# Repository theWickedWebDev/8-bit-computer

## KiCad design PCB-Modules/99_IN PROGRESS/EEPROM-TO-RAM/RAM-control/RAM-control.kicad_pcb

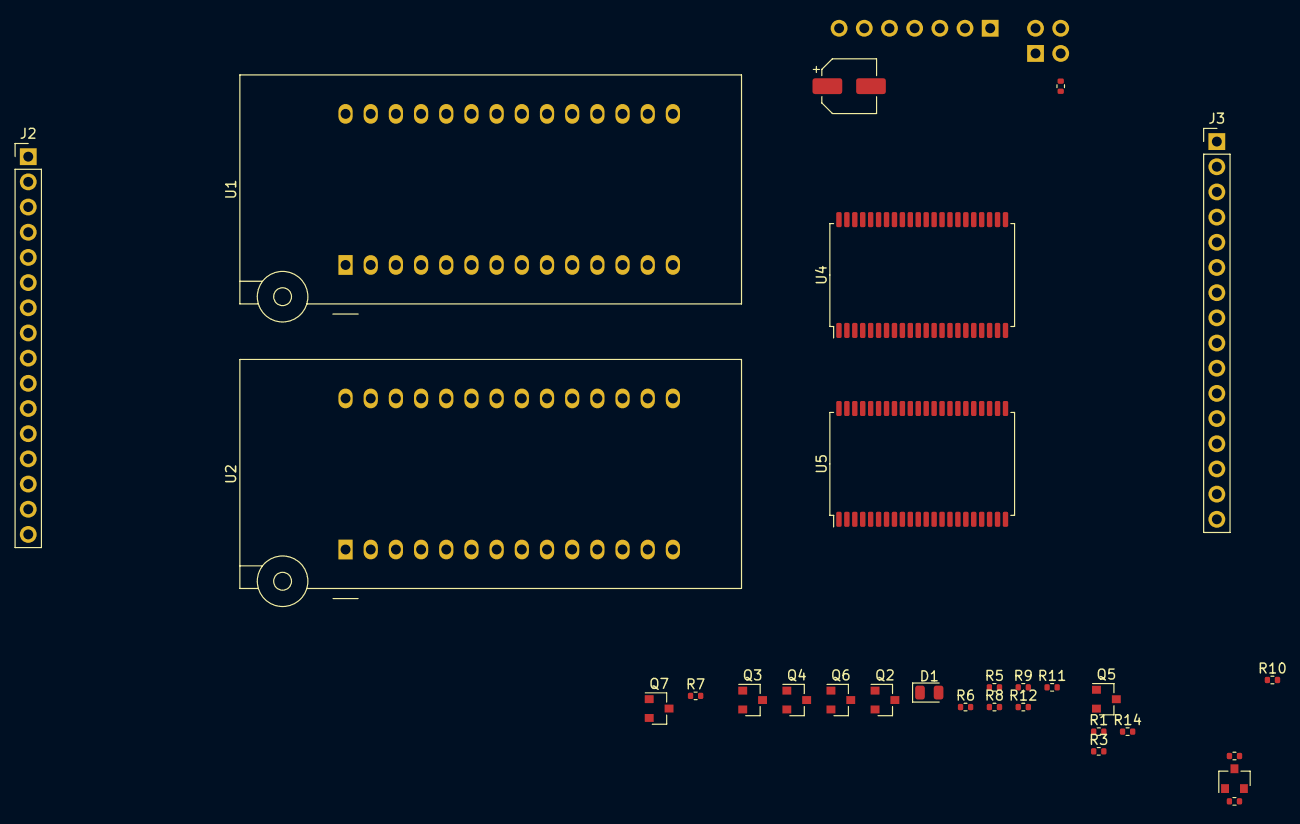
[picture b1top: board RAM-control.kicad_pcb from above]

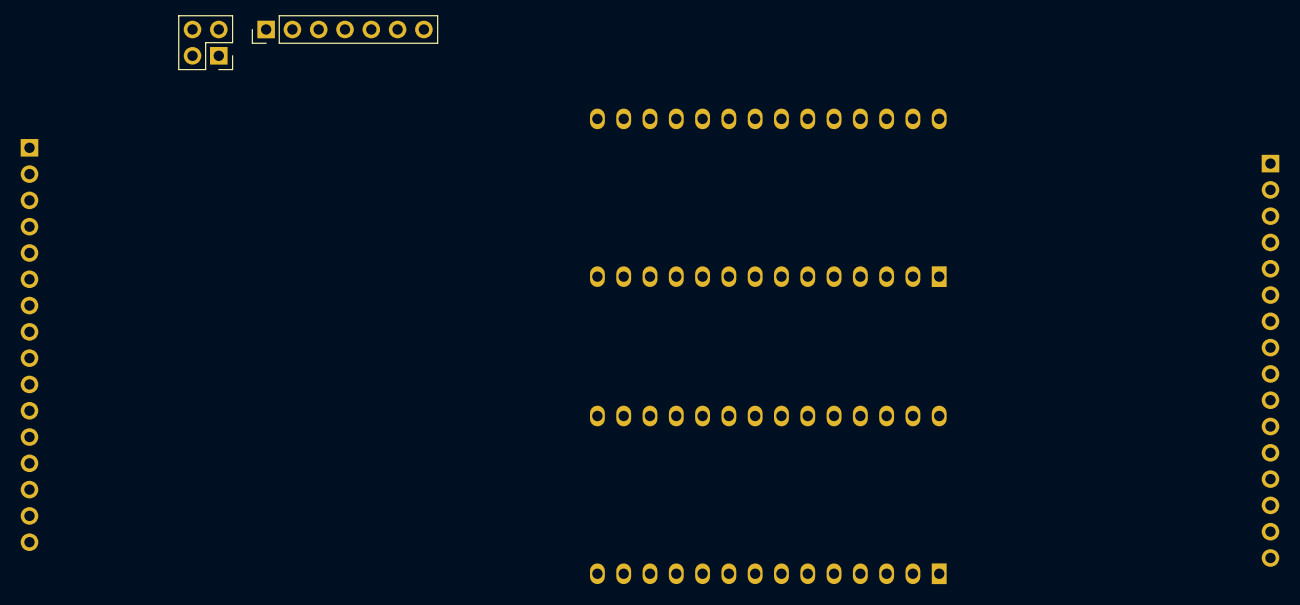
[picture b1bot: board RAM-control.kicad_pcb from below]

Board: 2 copper layers, 31 parts (2 on the bottom side), 55 nets, no tracks yet.

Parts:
C1: SMD-ECAP-5x5.8; CP_Elec_5x5.8
D1: NCD0805R1; LED_0805_2012Metric
J1: Conn_01x07; PinHeader_1x07_P2.54mm_Vertical
J2, J3: Conn_01x16; PinHeader_1x16_P2.54mm_Vertical
J4: Conn_02x02; PinHeader_2x02_P2.54mm_Vertical
Q1: DDTD123YC-7-F; SOT-23
Q2, Q3, Q4, Q5, Q6, Q7: 2N3904S-RTK_PS; SOT-23
R1, R13, R14: 0402WGF1001TCE; R_0402_1005Metric
R2, R10, R11, R12: 0402WGF3901TCE; R_0402_1005Metric
R3, R4, R5, R6, R7, R8, R9: 0603WAF1002T5E; R_0402_1005Metric
U1, U2: 28C256; DIP_Socket-28_W11.9_W12.7_W15.24_W17.78_W18.5_3M_228-1277-0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
U4, U5: IS61WV25616BLL-10TLI; TSOP-II-44_10.16x18.41mm_P0.8mm

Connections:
A00: J2.16, U1.10, U2.10, U4.1, U5.1
A01: J2.15, U1.9, U2.9, U4.2, U5.2
A02: J2.14, U1.8, U2.8, U4.3, U5.3
A03: J2.13, U1.7, U2.7, U4.4, U5.4
A04: J2.12, U1.6, U2.6, U4.5, U5.5
A05: J2.11, U1.5, U2.5, U4.18, U5.18
A06: J2.10, U1.4, U2.4, U4.19, U5.19
A07: J2.9, U1.3, U2.3, U4.20, U5.20
A08: J2.8, U1.25, U2.25, U4.21, U5.21
A09: J2.7, U1.24, U2.24, U4.22, U5.22
A10: J2.6, U1.21, U2.21, U4.23, U5.23
A11: J2.5, U1.23, U2.23, U4.24, U5.24
A12: J2.4, U1.2, U2.2, U4.25, U5.25
A13: J2.3, U1.26, U2.26, U4.26, U5.26
A14: J2.2, U1.1, U2.1, U4.27, U5.27
A16: J4.3, J4.4, R14.2
A17: J4.1, J4.2, R13.2
CLOCK: J1.5, R6.1
D00: J3.16, U1.11, U4.7, U5.7
D01: J3.15, U1.12, U4.8, U5.8
D02: J3.14, U1.13, U4.9, U5.9
D03: J3.13, U1.15, U4.10, U5.10
D04: J3.12, U1.16, U4.13, U5.13
D05: J3.11, U1.17, U4.14, U5.14
D06: J3.10, U1.18, U4.15, U5.15
D07: J3.9, U1.19, U4.16, U5.16
D08: J3.8, U2.11, U4.29, U5.29
D09: J3.7, U2.12, U4.30, U5.30
D10: J3.6, U2.13, U4.31, U5.31
D11: J3.5, U2.15, U4.32, U5.32
D12: J3.4, U2.16, U4.35, U5.35
D13: J3.3, U2.17, U4.36, U5.36
D14: J3.2, U2.18, U4.37, U5.37
D15: J3.1, U2.19, U4.38, U5.38
DATA_REQ: J1.1, R4.1, R7.1
GND: C1.2, J1.6, Q1.2, Q2.1, Q3.1, Q4.1, R1.2, R13.1, R14.1, U1.14, U2.14, U4.12, U4.34, U4.39, U4.40, U4.43, U4.44, U5.12, U5.34, U5.39, U5.40, U5.43, U5.44
unnamed: D1.1, R1.1
unnamed: Q1.1, R4.2
unnamed: Q1.3, R2.2, R8.1
unnamed: Q2.2, R3.2
unnamed: Q2.3, Q5.1
unnamed: Q3.2, R5.2
unnamed: Q3.3, Q6.1
unnamed: Q4.2, R6.2
unnamed: Q4.3, Q7.1
unnamed: Q5.2, R7.2
unnamed: Q6.2, R8.2
unnamed: Q7.2, R9.2
VCC: C1.1, D1.2, J1.7, R2.1, R10.2, R11.2, R12.2, U1.27, U1.28, U2.27, U2.28, U4.11, U4.33, U5.11, U5.33
WE: J1.4, R9.1
~CODE_RAM_EN: Q5.3, R10.1, U4.6
~DATA_RAM_EN: Q6.3, R11.1, U5.6
~OE: J1.3, U1.22, U2.22, U4.41, U5.41
~RAM_WE: Q7.3, R12.1, U4.17, U5.17
~ROM_EN~_A15: J1.2, R3.1, R5.1, U1.20, U2.20, U4.42, U5.42

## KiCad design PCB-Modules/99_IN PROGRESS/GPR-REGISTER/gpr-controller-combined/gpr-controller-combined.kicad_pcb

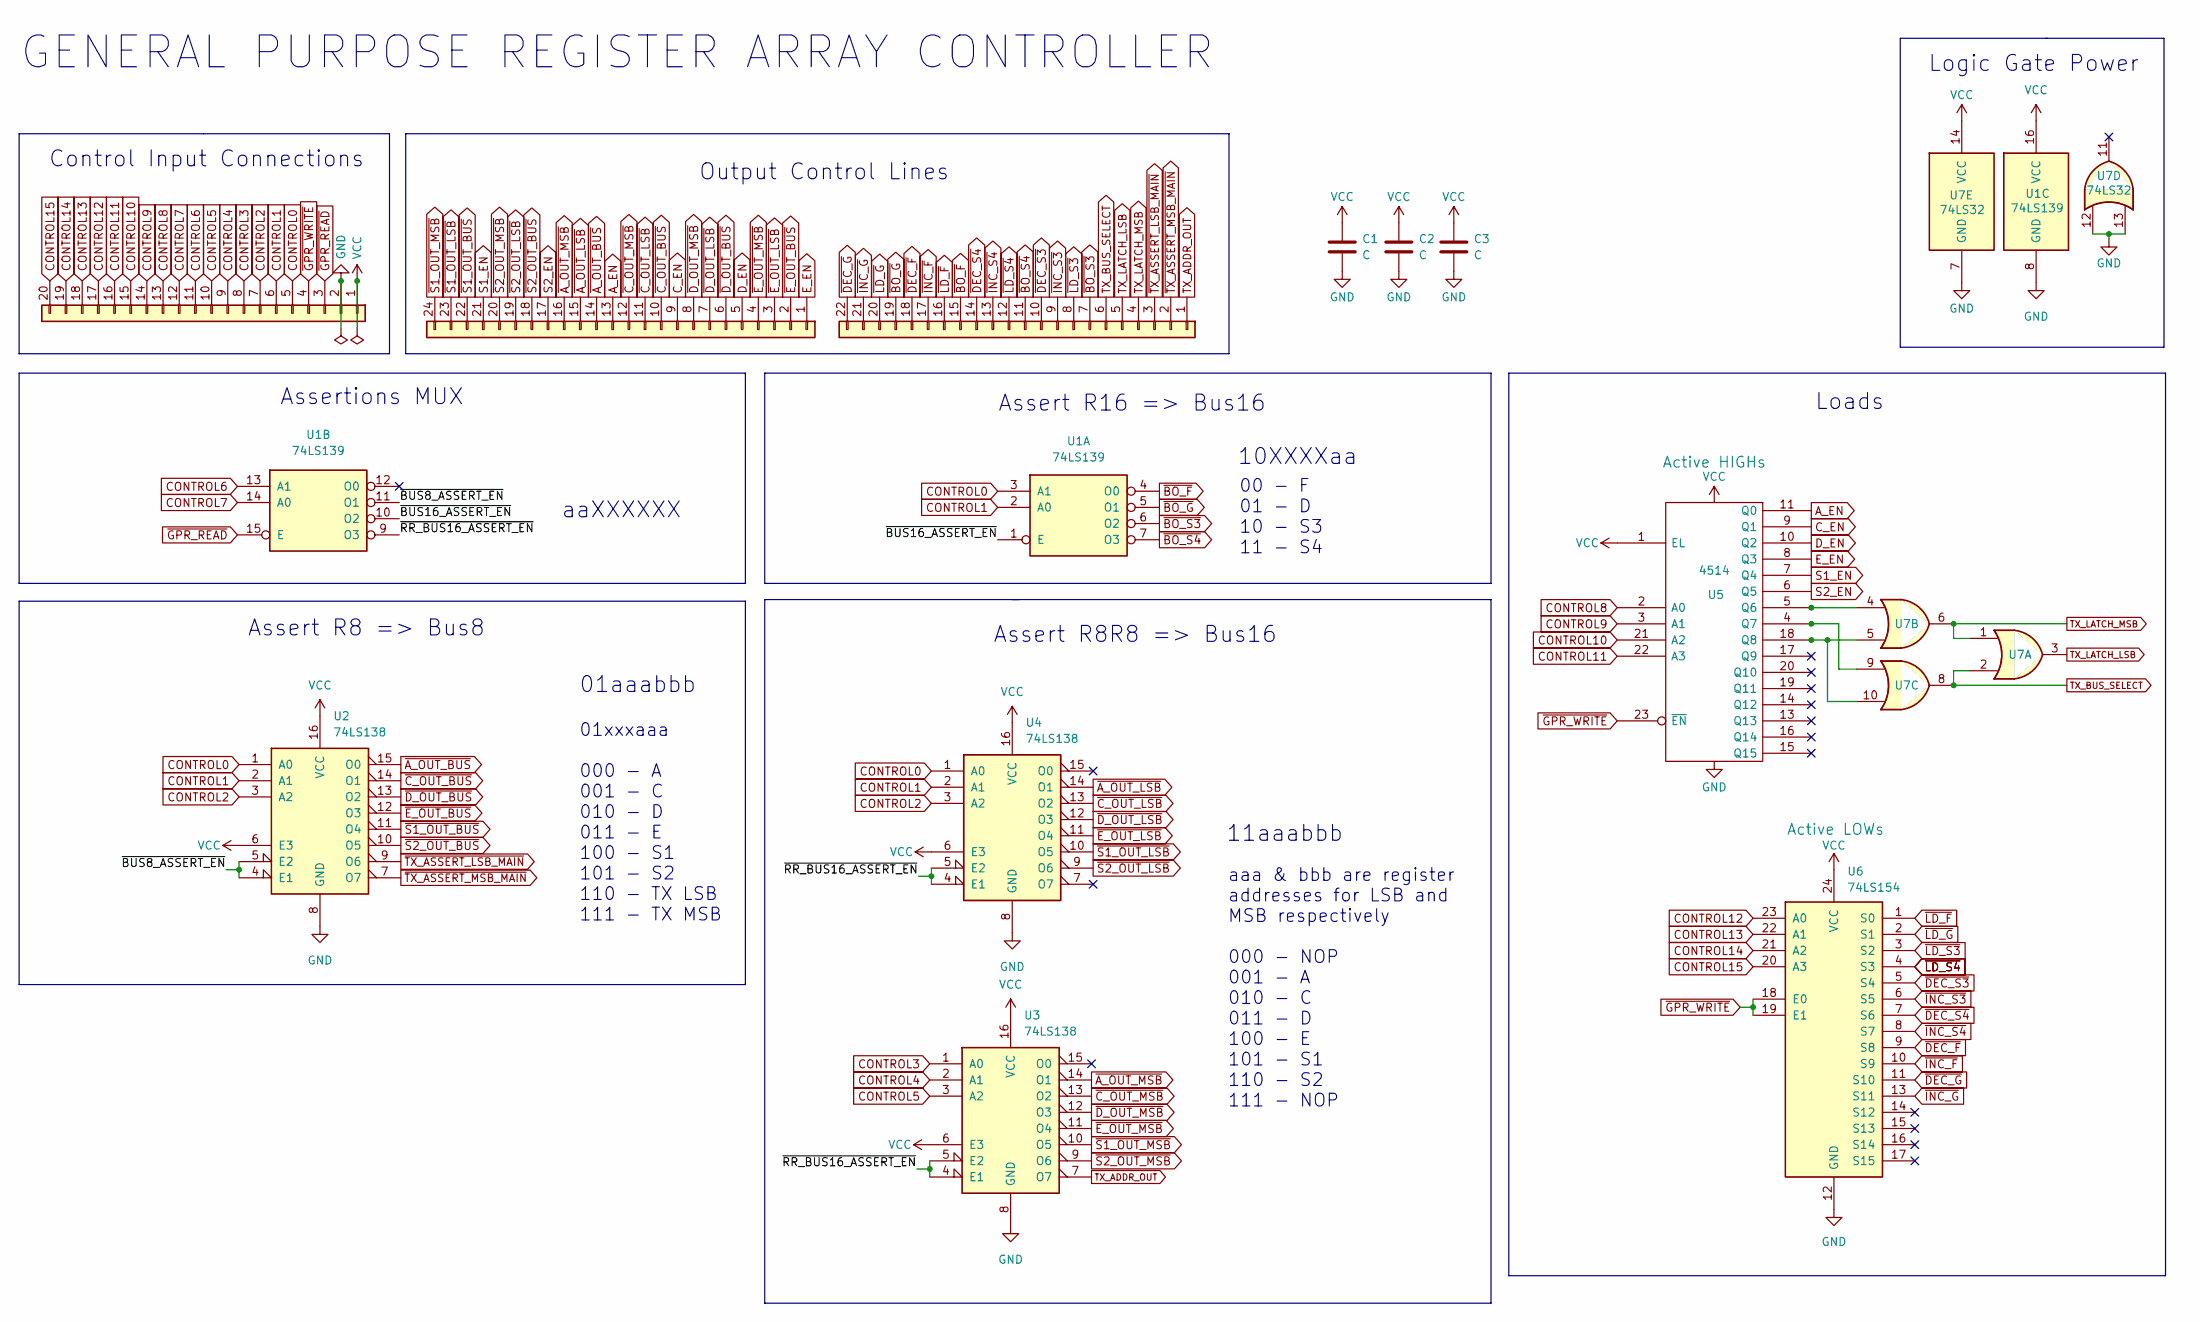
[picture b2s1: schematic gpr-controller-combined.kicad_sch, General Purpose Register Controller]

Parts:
C1, C2, C3: C; C_0805_2012Metric
J1: Conn_01x21; PinHeader_1x20_P2.54mm_Vertical
J2: Conn_01x24; PinHeader_1x24_P2.54mm_Vertical
J3: Conn_01x22; PinHeader_1x22_P2.54mm_Vertical
U1: 74LS139; TSSOP-16_4.4x5mm_P0.65mm
U2, U3, U4: 74LS138; TSSOP-16_4.4x5mm_P0.65mm
U5: 4514; SOP-24_7.5x15.4mm_P1.27mm
U6: 74LS154; SOP-24_7.5x15.4mm_P1.27mm
U7: 74LS32; TSSOP-14_4.4x5mm_P0.65mm

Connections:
/~BUS8_ASSERT_EN: U1.11 (O1), U2.4 (E1), U2.5 (E2)
/~BUS16_ASSERT_EN: U1.1 (E), U1.10 (O2)
/~RR_BUS16_ASSERT_EN: U1.9 (O3), U3.4 (E1), U3.5 (E2), U4.4 (E1), U4.5 (E2)
A_EN: J2.13, U5.11 (Q0)
CONTROL0: J1.5, U1.3 (A1), U2.1 (A0), U4.1 (A0)
CONTROL1: J1.6, U1.2 (A0), U2.2 (A1), U4.2 (A1)
CONTROL2: J1.7, U2.3 (A2), U4.3 (A2)
CONTROL3: J1.8, U3.1 (A0)
CONTROL4: J1.9, U3.2 (A1)
CONTROL5: J1.10, U3.3 (A2)
CONTROL6: J1.11, U1.13 (A1)
CONTROL7: J1.12, U1.14 (A0)
CONTROL8: J1.13, U5.2 (A0)
CONTROL9: J1.14, U5.3 (A1)
CONTROL10: J1.15, U5.21 (A2)
CONTROL11: J1.16, U5.22 (A3)
CONTROL12: J1.17, U6.23 (A0)
CONTROL13: J1.18, U6.22 (A1)
CONTROL14: J1.19, U6.21 (A2)
CONTROL15: J1.20, U6.20 (A3)
C_EN: J2.9, U5.9 (Q1)
D_EN: J2.5, U5.10 (Q2)
E_EN: J2.1, U5.8 (Q3)
GND: C1.2, C2.2, C3.2, J1.2, U1.8 (GND), U2.8 (GND), U3.8 (GND), U4.8 (GND), U5.12 (Vss), U6.12 (GND), U7.7 (GND), U7.12, U7.13
unnamed: U5.4 (Q7), U7.9
unnamed: U5.5 (Q6), U7.4
unnamed: U5.18 (Q8), U7.5, U7.10
S1_EN: J2.21, U5.7 (Q4)
S2_EN: J2.17, U5.6 (Q5)
TX_ADDR_OUT: J3.1, U3.7 (O7)
TX_BUS_SELECT: J3.6, U7.2, U7.8
TX_LATCH_LSB: J3.5, U7.3
TX_LATCH_MSB: J3.4, U7.1, U7.6
VCC: C1.1, C2.1, C3.1, J1.1, U1.16 (VCC), U2.6 (E3), U2.16 (VCC), U3.6 (E3), U3.16 (VCC), U4.6 (E3), U4.16 (VCC), U5.1 (EL), U5.24 (Vdd), U6.24 (VCC), U7.14 (VCC)
~A_OUT_BUS: J2.14, U2.15 (O0)
~A_OUT_LSB: J2.15, U4.14 (O1)
~A_OUT_MSB: J2.16, U3.14 (O1)
~BO_F: J3.15, U1.4 (O0)
~BO_G: J3.19, U1.5 (O1)
~BO_S3: J3.7, U1.6 (O2)
~BO_S4: J3.11, U1.7 (O3)
~C_OUT_BUS: J2.10, U2.14 (O1)
~C_OUT_LSB: J2.11, U4.13 (O2)
~C_OUT_MSB: J2.12, U3.13 (O2)
~DEC_F: J3.18, U6.9 (S8)
~DEC_G: J3.22, U6.11 (S10)
~DEC_S3: J3.10, U6.5 (S4)
~DEC_S4: J3.14, U6.7 (S6)
~D_OUT_BUS: J2.6, U2.13 (O2)
~D_OUT_LSB: J2.7, U4.12 (O3)
~D_OUT_MSB: J2.8, U3.12 (O3)
~E_OUT_BUS: J2.2, U2.12 (O3)
~E_OUT_LSB: J2.3, U4.11 (O4)
~E_OUT_MSB: J2.4, U3.11 (O4)
~GPR_READ: J1.3, U1.15 (E)
~GPR_WRITE: J1.4, U5.23 (~EN), U6.18 (E0), U6.19 (E1)
~INC_F: J3.17, U6.10 (S9)
~INC_G: J3.21, U6.13 (S11)
~INC_S3: J3.9, U6.6 (S5)
~INC_S4: J3.13, U6.8 (S7)
~LD_F: J3.16, U6.1 (S0)
~LD_G: J3.20, U6.2 (S1)
~LD_S3: J3.8, U6.3 (S2)
~LD_S4: J3.12, U6.4 (S3)
~S1_OUT_BUS: J2.22, U2.11 (O4)
~S1_OUT_LSB: J2.23, U4.10 (O5)
~S1_OUT_MSB: J2.24, U3.10 (O5)
~S2_OUT_BUS: J2.18, U2.10 (O5)
~S2_OUT_LSB: J2.19, U4.9 (O6)
~S2_OUT_MSB: J2.20, U3.9 (O6)
~TX_ASSERT_LSB_MAIN: J3.3, U2.9 (O6)
~TX_ASSERT_MSB_MAIN: J3.2, U2.7 (O7)

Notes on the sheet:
01aaabbb
Assert R8 => Bus8
Loads
00 - F 01 - D 10 - S3 11 - S4
11aaabbb
10XXXXaa
aaa & bbb are register addresses for LSB and MSB respectively 000 - NOP 001 - A 010 - C 011 - D 100 - E 101 - S1 110 - S2 111 - NOP
Assert R16 => Bus16
aaXXXXXX
GENERAL PURPOSE REGISTER ARRAY CONTROLLER
Control Input Connections
Assertions MUX
Output Control Lines
01xxxaaa 000 - A 001 - C 010 - D 011 - E 100 - S1 101 - S2 110 - TX LSB 111 - TX MSB
Assert R8R8 => Bus16
Logic Gate Power

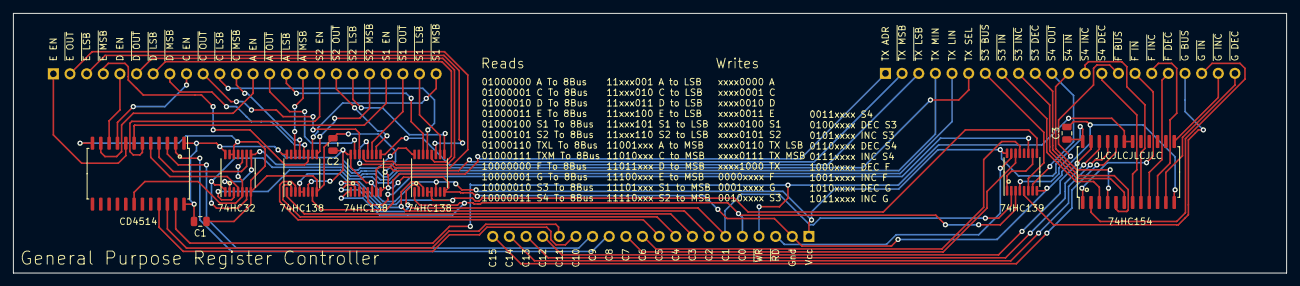
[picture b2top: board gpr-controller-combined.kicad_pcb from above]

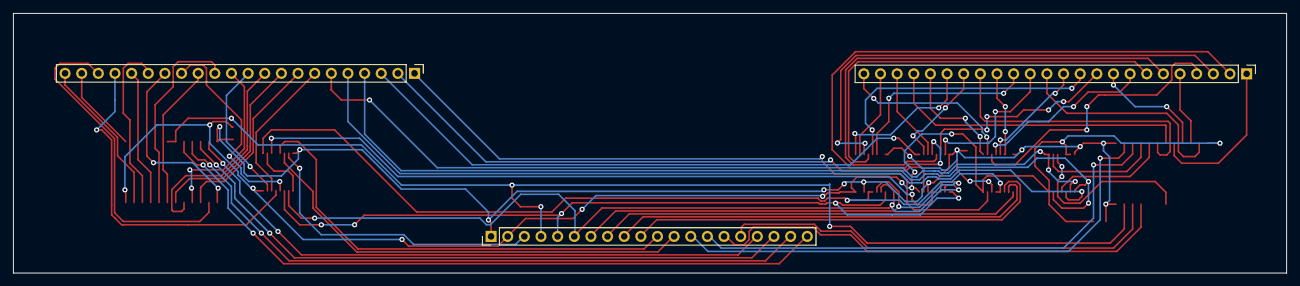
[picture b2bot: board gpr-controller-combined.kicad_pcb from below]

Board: 2 copper layers, 194.3 x 39.6 mm, 13 parts (3 on the bottom side), 72 nets.

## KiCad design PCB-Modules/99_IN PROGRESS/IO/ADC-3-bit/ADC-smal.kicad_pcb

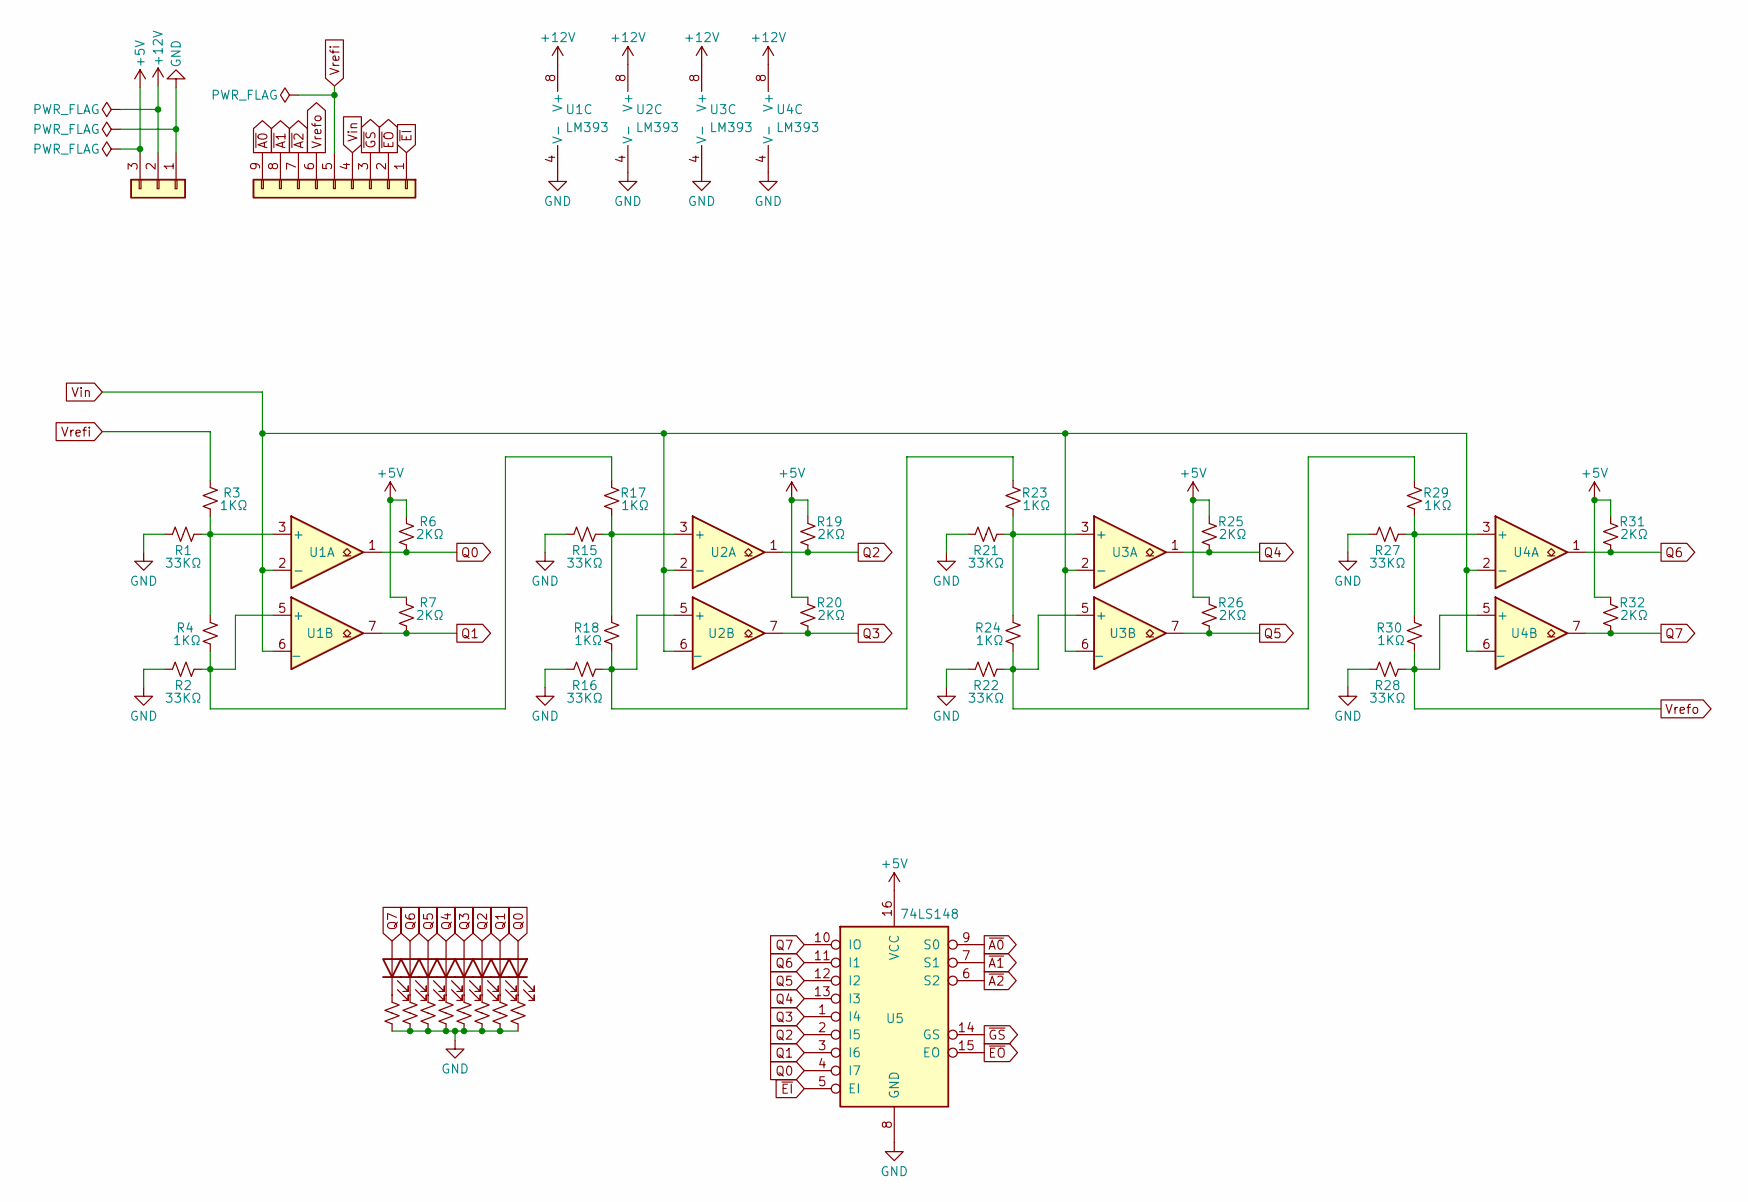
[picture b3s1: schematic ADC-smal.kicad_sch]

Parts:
D1, D2, D3, D4, D5, D6, D7, D8: LED; LED_0805_2012Metric
J1: Conn_01x03; PinHeader_1x03_P2.54mm_Vertical
J2: Conn_01x09; PinHeader_1x09_P2.54mm_Vertical
R1, R2, R3, R4, R5, R6, R7, R8, R9, R10, R11, R12, R13, R14, R15, R16, R17, R18, R19, R20, R21, R22, R23, R24, R25, R26, R27, R28, R29, R30, R31, R32: R_Small_US; R_0805_2012Metric
U1, U2, U3, U4: LM393; SOIC-8_3.9x4.9mm_P1.27mm
U5: 74LS148; SOIC-16_3.9x9.9mm_P1.27mm

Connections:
+5V: J1.3, R6.2, R7.2, R19.2, R20.2, R25.2, R26.2, R31.2, R32.2, U5.16 (VCC)
+12V: J1.2, U1.8 (V+), U2.8 (V+), U3.8 (V+), U4.8 (V+)
GND: J1.1, R1.1, R2.1, R5.2, R8.2, R9.2, R10.2, R11.2, R12.2, R13.2, R14.2, R15.1, R16.1, R21.1, R22.1, R27.1, R28.1, U1.4 (V-), U2.4 (V-), U3.4 (V-), U4.4 (V-), U5.8 (GND)
unnamed: D1.1 (K), R5.1
unnamed: D2.1 (K), R8.1
unnamed: D3.1 (K), R9.1
unnamed: D4.1 (K), R10.1
unnamed: D5.1 (K), R11.1
unnamed: D6.1 (K), R12.1
unnamed: D7.1 (K), R13.1
unnamed: D8.1 (K), R14.1
unnamed: R1.2, R3.2, R4.1, U1.3 (+)
unnamed: R15.2, R17.2, R18.1, U2.3 (+)
unnamed: R16.2, R18.2, R23.1, U2.5 (+)
unnamed: R2.2, R4.2, R17.1, U1.5 (+)
unnamed: R21.2, R23.2, R24.1, U3.3 (+)
unnamed: R22.2, R24.2, R29.1, U3.5 (+)
unnamed: R27.2, R29.2, R30.1, U4.3 (+)
Q0: D8.2 (A), R6.1, U1.1, U5.4 (I7)
Q1: D7.2 (A), R7.1, U1.7, U5.3 (I6)
Q2: D6.2 (A), R19.1, U2.1, U5.2 (I5)
Q3: D5.2 (A), R20.1, U2.7, U5.1 (I4)
Q4: D4.2 (A), R25.1, U3.1, U5.13 (I3)
Q5: D3.2 (A), R26.1, U3.7, U5.12 (I2)
Q6: D2.2 (A), R31.1, U4.1, U5.11 (I1)
Q7: D1.2 (A), R32.1, U4.7, U5.10 (IO)
Vin: J2.4, U1.2 (-), U1.6 (_), U2.2 (-), U2.6 (_), U3.2 (-), U3.6 (_), U4.2 (-), U4.6 (_)
Vrefi: J2.5, R3.1
Vrefo: J2.6, R28.2, R30.2, U4.5 (+)
~A0: J2.9, U5.9 (S0)
~A1: J2.8, U5.7 (S1)
~A2: J2.7, U5.6 (S2)
~EI: J2.1, U5.5 (EI)
~EO: J2.2, U5.15 (EO)
~GS: J2.3, U5.14 (GS)

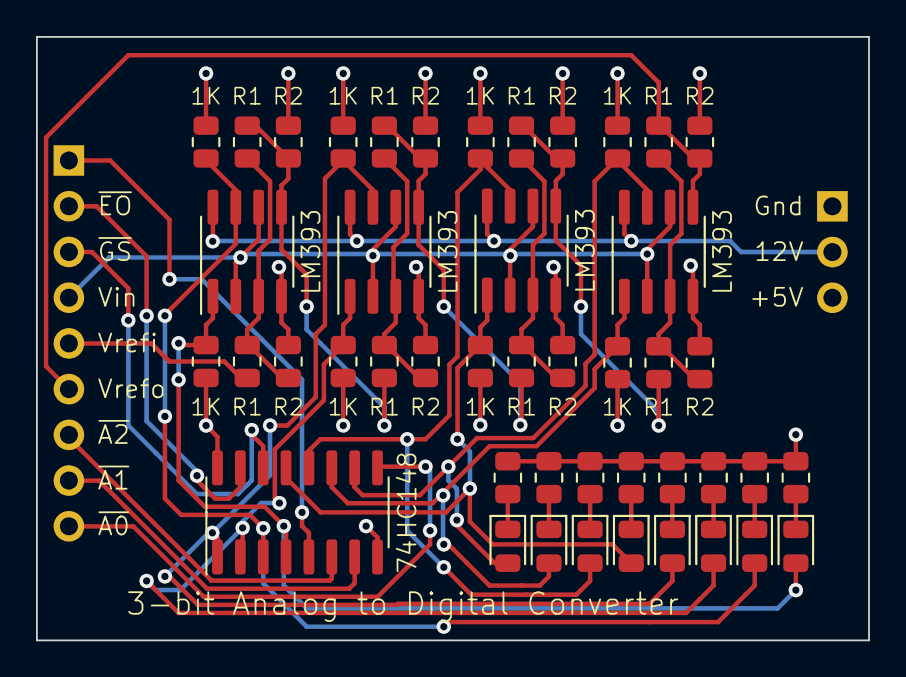
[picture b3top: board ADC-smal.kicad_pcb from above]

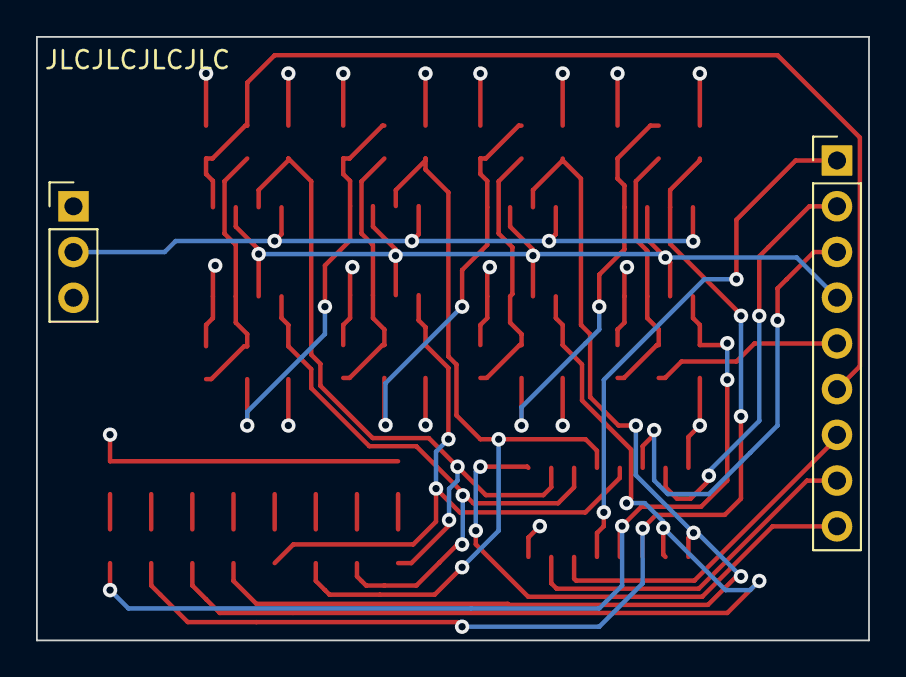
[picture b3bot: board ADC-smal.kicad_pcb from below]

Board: 4 copper layers, 46.2 x 33.5 mm, 47 parts (2 on the bottom side), 35 nets.

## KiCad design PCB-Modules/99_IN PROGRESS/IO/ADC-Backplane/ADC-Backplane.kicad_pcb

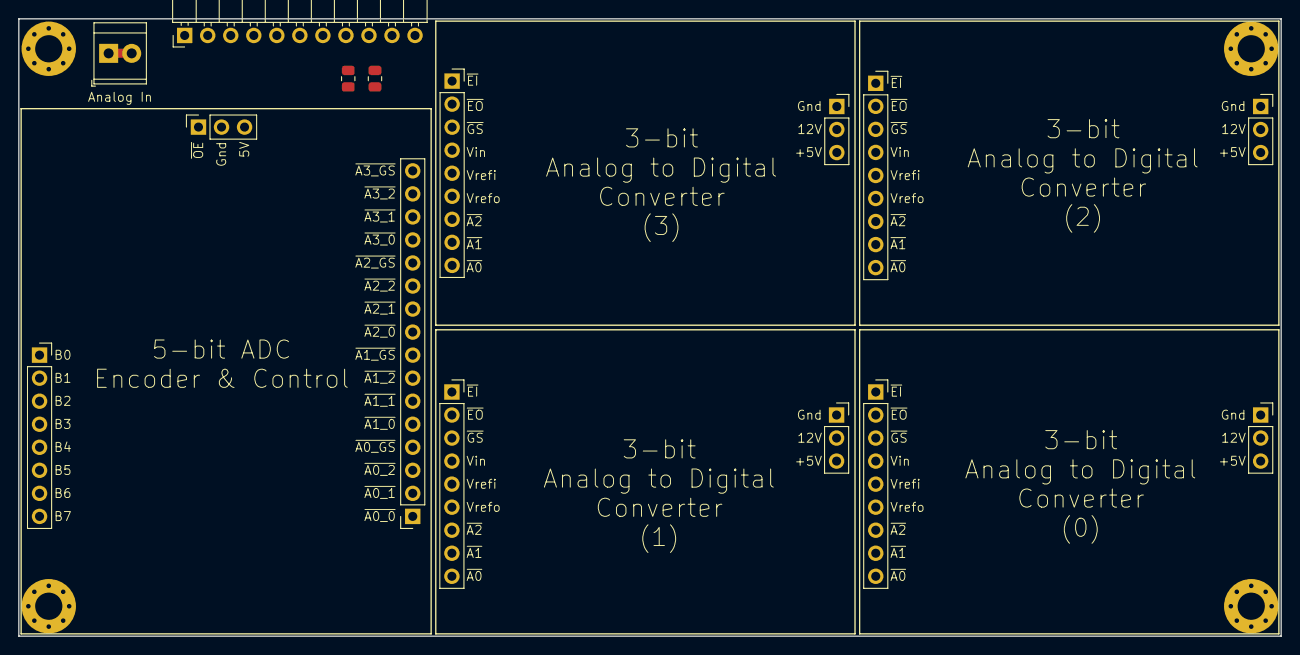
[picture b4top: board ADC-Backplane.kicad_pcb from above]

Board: 4 copper layers, 139.2 x 68.1 mm, 15 parts (0 on the bottom side), 33 nets.

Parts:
J1: Conn_01x11; PinHeader_1x11_P2.54mm_Horizontal
J2, J4, J6, J8: Conn_01x09; PinSocket_1x09_P2.54mm_Vertical
J3, J5, J7, J9, J10: Conn_01x03; PinSocket_1x03_P2.54mm_Vertical
J11: Conn_01x16; PinSocket_1x16_P2.54mm_Vertical
J12: Conn_01x08; PinSocket_1x08_P2.54mm_Vertical
J13: Screw_Terminal_01x02; TerminalBlock_TE_282834-2_1x02_P2.54mm_Horizontal
R1, R2: R_Small_US; R_0805_2012Metric

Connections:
BUS0: J1.4, J12.1
BUS1: J1.5, J12.2
BUS2: J1.6, J12.3
BUS3: J1.7, J12.4
BUS4: J1.8, J12.5
BUS5: J1.9, J12.6
BUS6: J1.10, J12.7
BUS7: J1.11, J12.8
GND: J1.2, J3.1, J5.1, J7.1, J8.1, J9.1, R2.2
unnamed: J2.5, J4.6
unnamed: J2.1, J4.2
unnamed: J4.5, J6.6
unnamed: J6.1, J8.2
unnamed: J4.1, J6.2
unnamed: J6.5, J8.6
unnamed: J8.5, R1.1, R2.1
~A0_0: J8.9, J11.1
~A0_1: J8.8, J11.2
~A0_2: J8.7, J11.3
~A0_GS: J8.3, J11.4
~A1_0: J6.9, J11.5
~A1_1: J6.8, J11.6
~A1_2: J6.7, J11.7
~A1_GS: J6.3, J11.8
~A2_0: J4.9, J11.9
~A2_1: J4.8, J11.10
~A2_2: J4.7, J11.11
~A2_GS: J4.3, J11.12
~A3_0: J2.9, J11.13
~A3_1: J2.8, J11.14
~A3_2: J2.7, J11.15
~A3_GS: J2.3, J11.16
~ANALOG_IN: J2.4, J4.4, J6.4, J8.4, J13.1, J13.2

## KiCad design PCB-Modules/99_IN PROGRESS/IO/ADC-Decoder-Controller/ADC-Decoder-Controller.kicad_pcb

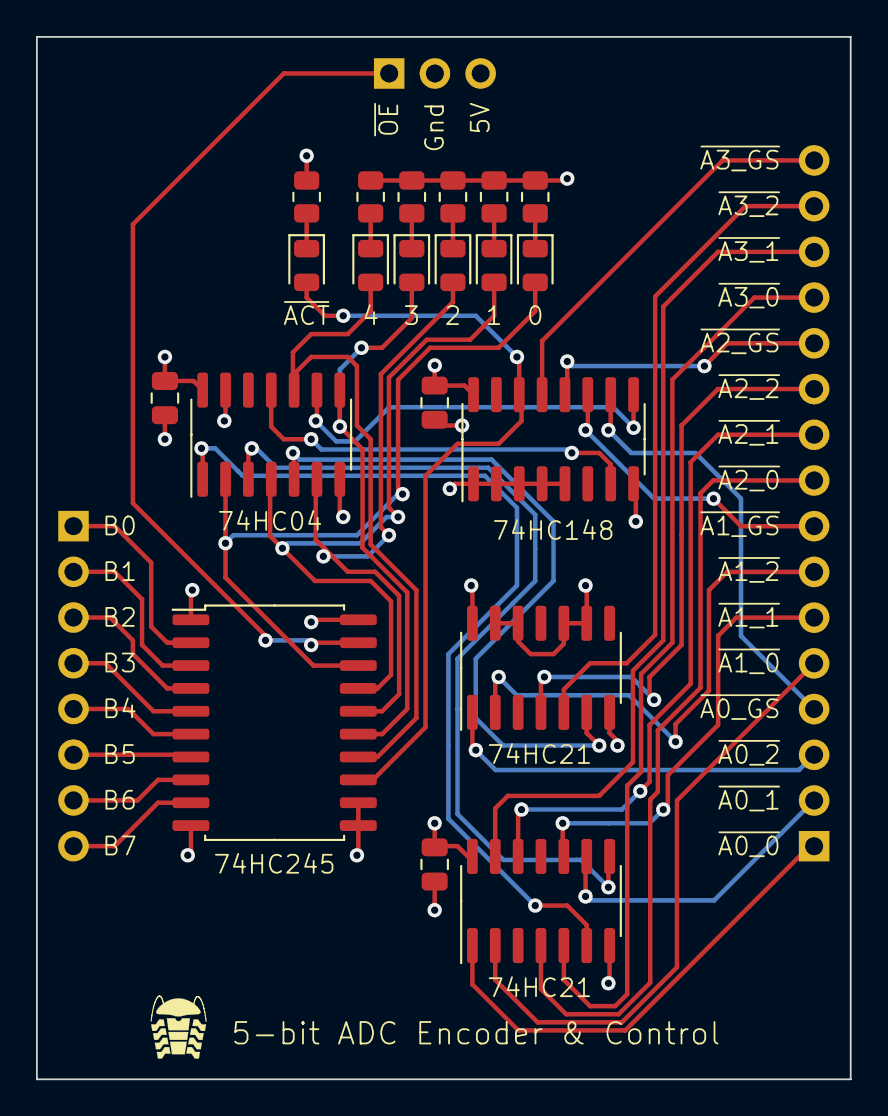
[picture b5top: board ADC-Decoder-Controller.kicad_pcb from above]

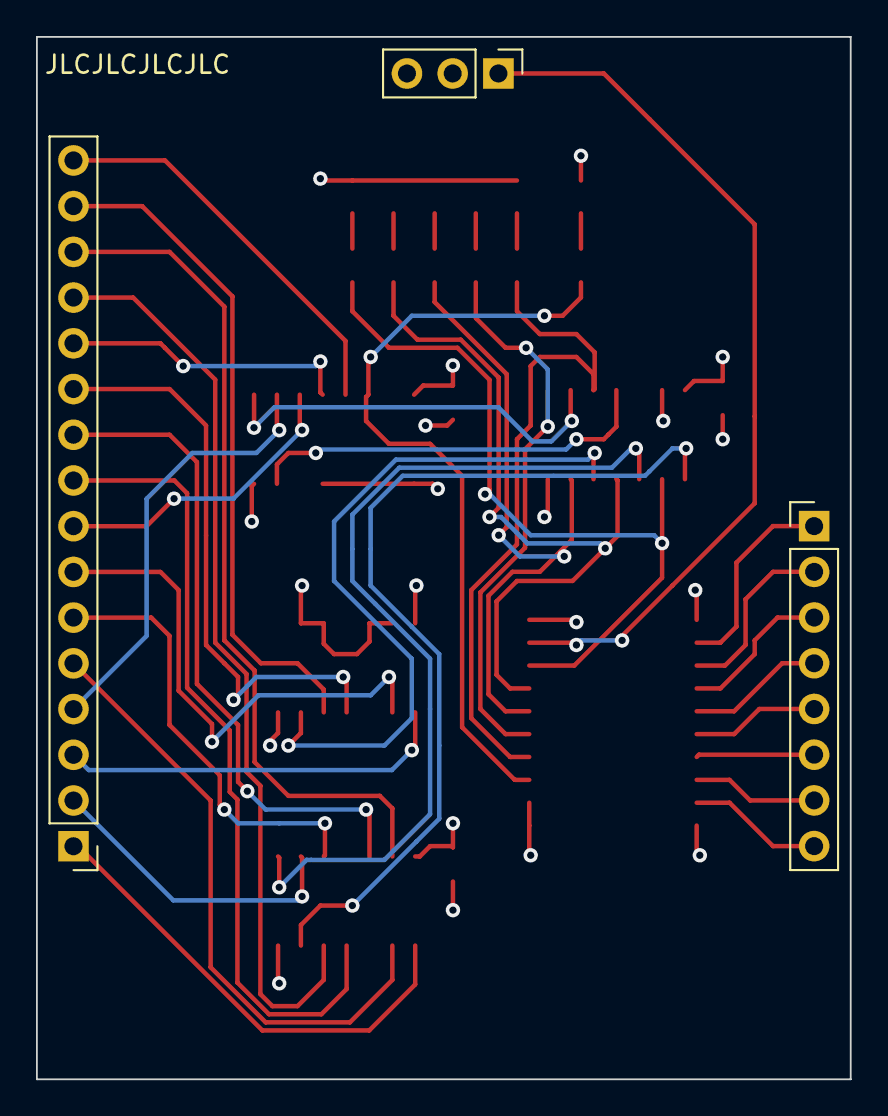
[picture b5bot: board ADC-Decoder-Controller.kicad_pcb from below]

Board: 4 copper layers, 45.2 x 57.9 mm, 23 parts (3 on the bottom side), 44 nets.

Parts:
C1, C2, C3: C_Small; C_0805_2012Metric
D1, D2, D3, D4, D5, D6: LED; LED_0805_2012Metric
J1: Conn_01x08; PinHeader_1x08_P2.54mm_Vertical
J2: Conn_01x16; PinHeader_1x16_P2.54mm_Vertical
J3: Conn_01x03; PinHeader_1x03_P2.54mm_Vertical
R3, R4, R5, R6, R7, R8: R_Small_US; R_0805_2012Metric
U1, U2: 74LS21; SOIC-14_3.9x8.7mm_P1.27mm
U3: 74LS148; SOIC-16_3.9x9.9mm_P1.27mm
U4: 74LS04; SOIC-14_3.9x8.7mm_P1.27mm
U5: 74LS245; SOIC-20W_7.5x12.8mm_P1.27mm

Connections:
+5V: C1.1, C2.1, C3.1, J3.3, U1.14 (VCC), U2.14 (VCC), U3.1 (I4), U3.2 (I5), U3.3 (I6), U3.4 (I7), U3.5 (EI), U3.16 (VCC), U4.14 (VCC), U5.20 (VCC)
BUS0: J1.1, U5.2 (A0)
BUS1: J1.2, U5.3 (A1)
BUS2: J1.3, U5.4 (A2)
BUS3: J1.4, U5.5 (A3)
BUS4: J1.5, U5.6 (A4)
BUS5: J1.6, U5.7 (A5)
BUS6: J1.7, U5.8 (A6)
BUS7: J1.8, U5.9 (A7)
D0: D6.2 (A), U4.2, U5.18 (B0)
D1: D5.2 (A), U4.4, U5.17 (B1)
D2: D4.2 (A), U4.6, U5.16 (B2)
D3: D3.2 (A), U4.8, U5.15 (B3)
D4: D2.2 (A), U4.10, U5.14 (B4)
GND: C1.2, C2.2, C3.2, J3.2, R3.2, R4.2, R5.2, R6.2, R7.2, R8.2, U1.7 (GND), U2.7 (GND), U2.9, U2.10, U2.12, U2.13, U3.8 (GND), U4.7 (GND), U4.13, U5.1 (A->B), U5.10 (GND), U5.11 (B7), U5.12 (B6)
unnamed: D1.1 (K), R3.1
unnamed: D2.1 (K), R4.1
unnamed: D3.1 (K), R5.1
unnamed: D4.1 (K), R6.1
unnamed: D5.1 (K), R7.1
unnamed: D6.1 (K), R8.1
unnamed: U1.6, U4.1
unnamed: U1.8, U4.3
unnamed: U2.6, U4.5
unnamed: U3.7 (S1), U4.11
unnamed: U3.9 (S0), U4.9
~A0_0: J2.1, U1.1
~A0_1: J2.2, U1.9
~A0_2: J2.3, U2.1
~A0_GS: J2.4, U3.10 (IO)
~A1_0: J2.5, U1.2
~A1_1: J2.6, U1.10
~A1_2: J2.7, U2.2
~A1_GS: J2.8, U3.11 (I1)
~A2_0: J2.9, U1.4
~A2_1: J2.10, U1.12
~A2_2: J2.11, U2.4
~A2_GS: J2.12, U3.12 (I2)
~A3_0: J2.13, U1.5
~A3_1: J2.14, U1.13
~A3_2: J2.15, U2.5
~A3_GS: J2.16, U3.13 (I3)
~ACTIVE: D1.2 (A), U3.14 (GS), U5.13 (B5)
~OE: J3.1, U5.19 (CE)

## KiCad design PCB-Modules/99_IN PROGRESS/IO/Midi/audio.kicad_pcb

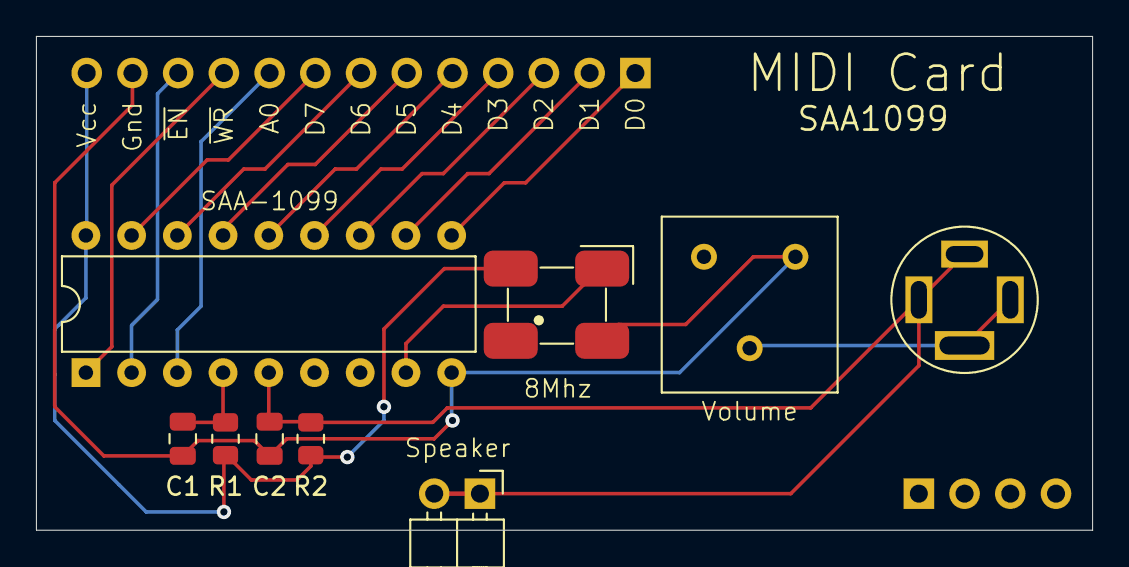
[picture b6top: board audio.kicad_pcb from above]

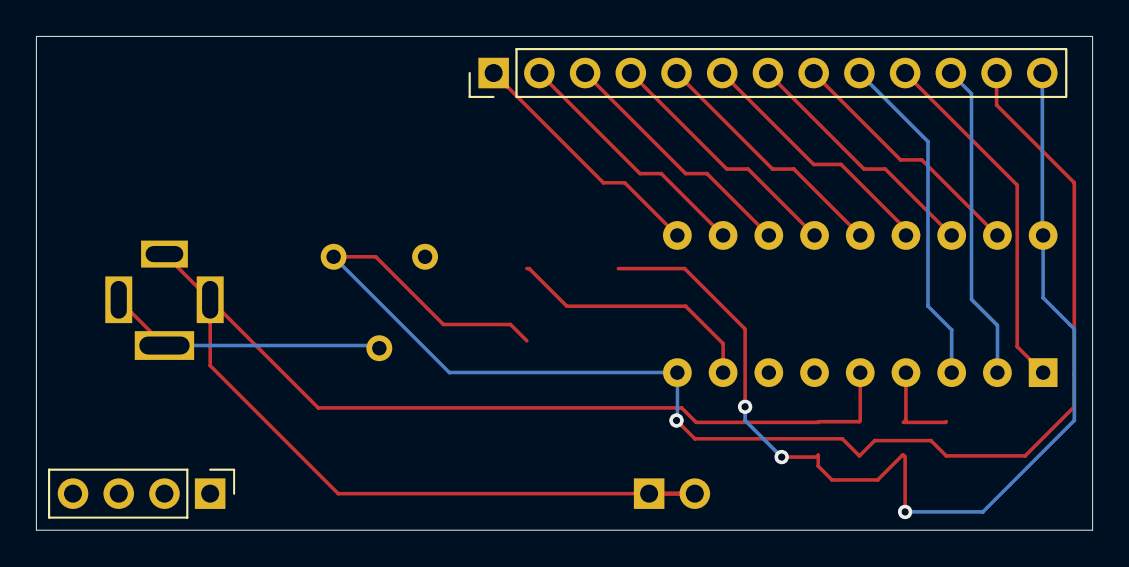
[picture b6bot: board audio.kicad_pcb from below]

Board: 2 copper layers, 58.7 x 27.4 mm, 11 parts (2 on the bottom side), 17 nets.

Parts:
C1, C2: C; C_0805_2012Metric
J1: Conn_01x13; PinHeader_1x13_P2.54mm_Vertical
J2: Conn_01x04; PinHeader_1x04_P2.54mm_Vertical
J3: Conn_01x02; PinHeader_1x02_P2.54mm_Horizontal
LS1: Speaker; speaker-jack
R1, R2: R_Small_US; R_0805_2012Metric
RV1: R_POT_TRIM_US; Potentiometer_Bourns_3386F_Vertical
U1: SMD_Crystal; CFPS-72 SMD Clock
U2: SAA-1099; DIP-18_W7.62mm

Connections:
A4: J1.9, U2.3 (A0)
BUS0: J1.1, U2.10 (D0)
BUS1: J1.2, U2.11 (D1)
BUS2: J1.3, U2.12 (D2)
BUS3: J1.4, U2.13 (D3)
BUS4: J1.5, U2.14 (D4)
BUS5: J1.6, U2.15 (D5)
BUS6: J1.7, U2.16 (D6)
BUS7: J1.8, U2.17 (D7)
GND: C1.1, C2.1, J1.12, RV1.3, U1.2 (Gnd), U2.9 (GND)
unnamed: C1.2, R1.2, U2.4 (OUTR)
unnamed: LS1.R1, LS1.R2, RV1.2
unnamed: U1.3, U2.8 (CLK)
SPEAKER_OUT: C2.2, J3.1, J3.2, LS1.S, LS1.T, R2.2, U2.5 (OUTL)
VCC: J1.13, R1.1, R2.1, U1.4 (Vcc), U2.18 (VCC)
~EN: J1.11, U2.2 (~CS)
~WRITE: J1.10, U2.1 (~WR)
